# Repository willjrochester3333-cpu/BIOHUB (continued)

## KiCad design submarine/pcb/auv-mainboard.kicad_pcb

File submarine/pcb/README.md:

# PCB: the main board

A 150 x 60 mm, 2-layer carrier board for the ESP32-S3-DevKitC-1. It handles battery input, the 15 A fuse, the
magnet-operated soft-latch power switch, a 3 A 5 V regulator, the LoRa radio socket, all sensor connectors,
the 4-in-1 ESC interface, switched outputs, and camera power and button control.
How it works is explained in [`../docs/02-electronics.md`](../docs/02-electronics.md).

| Top | Bottom |
|---|---|
|  |  |

## Files

| File | What it is |
|---|---|
| `auv-mainboard.kicad_pro / .kicad_sch / .kicad_pcb` | The KiCad project (opens in KiCad 7 or newer) |
| `auv.kicad_sym`, `auv.pretty/` | Project library: ESP32-S3-DevKitC-1 socket and E220 socket symbols and footprints |
| `output/auv-mainboard-gerbers.zip` | **Upload this to JLCPCB / PCBWay.** Gerbers + drill files |
| `output/auv-mainboard-bom.csv` | Board parts list with suggested part numbers and rough prices |
| `output/auv-mainboard-pos.csv` | Pick-and-place file (if you want the board assembled) |
| `output/auv-mainboard-schematic.pdf / .png` | Schematic |
| `output/auv-mainboard-layout.pdf` | Top copper + silkscreen plot |
| `output/board_top.png`, `board_bottom.png` | Realistic images made from the Gerber layers |
| `design.py` | **Source of truth**: every part, pin, net, position and net class |
| `generate_board.py` | Turns `design.py` into everything above |
| `render_board_images.py` | Builds the board images from KiCad's layer plots |
| `placement.json` | Part positions and sizes for the Blender model |

## Status

* Schematic netlist (exported by KiCad) matches `design.py`: **0 mismatches**.
* Placement check: no courtyard overlaps. Only low SMD parts (≤ 3 mm) sit under the socketed DevKit and LoRa module.
* Routing: Freerouting 2.5, plus hand-placed wide copper for the battery -> fuse -> MOSFET -> ESC path
  (2.5–3 mm tracks, with the ground return on the bottom layer) and the regulator's switch node.
  Ground pours on both layers, and no copper under the ESP32 antenna.
* KiCad DRC: **0 errors, 0 unconnected pads**. The remaining warnings are silkscreen cosmetics and footprint-library
  links that need KiCad's global library table, which a normal KiCad install has.
* Fab limits used: 0.15 mm minimum track, 0.2 mm clearance, 0.35 mm minimum drill, 0.4 mm copper-to-edge.

## Regenerate

Needs KiCad 7+ (`pcbnew` Python module and `kicad-cli`), Java 25 and the Freerouting 2.5 jar. The board images need
Python with `cairosvg` and `Pillow`.

```bash
FREEROUTING_JAR=/path/to/freerouting-2.5.0-executable.jar python3 generate_board.py all
```

Steps, which can also be run one at a time: `libs sch verify_sch check route drc outputs`.

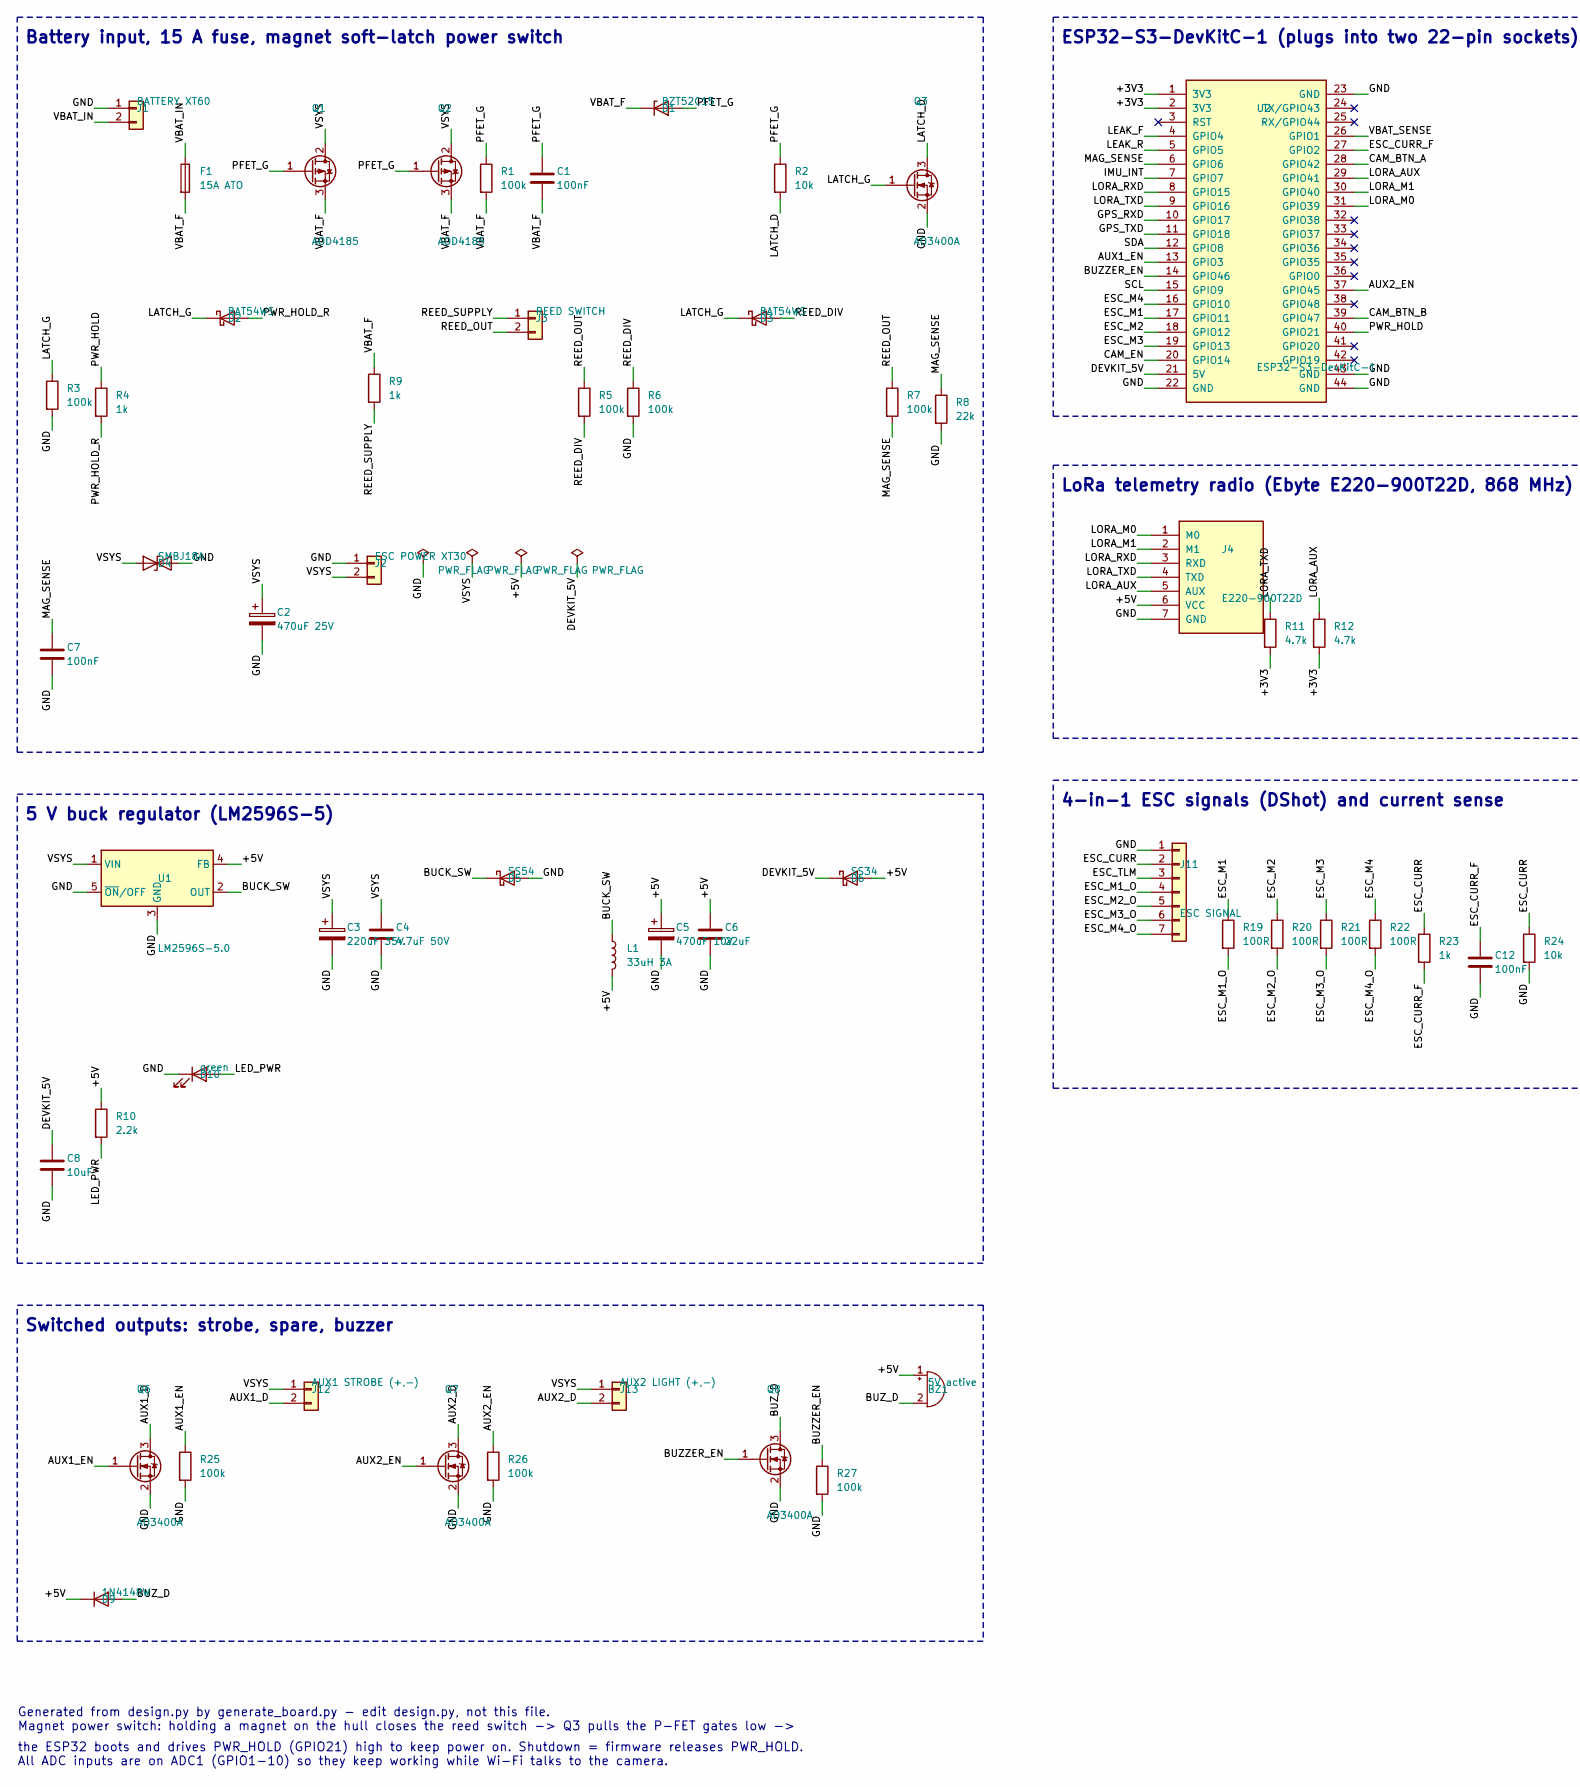
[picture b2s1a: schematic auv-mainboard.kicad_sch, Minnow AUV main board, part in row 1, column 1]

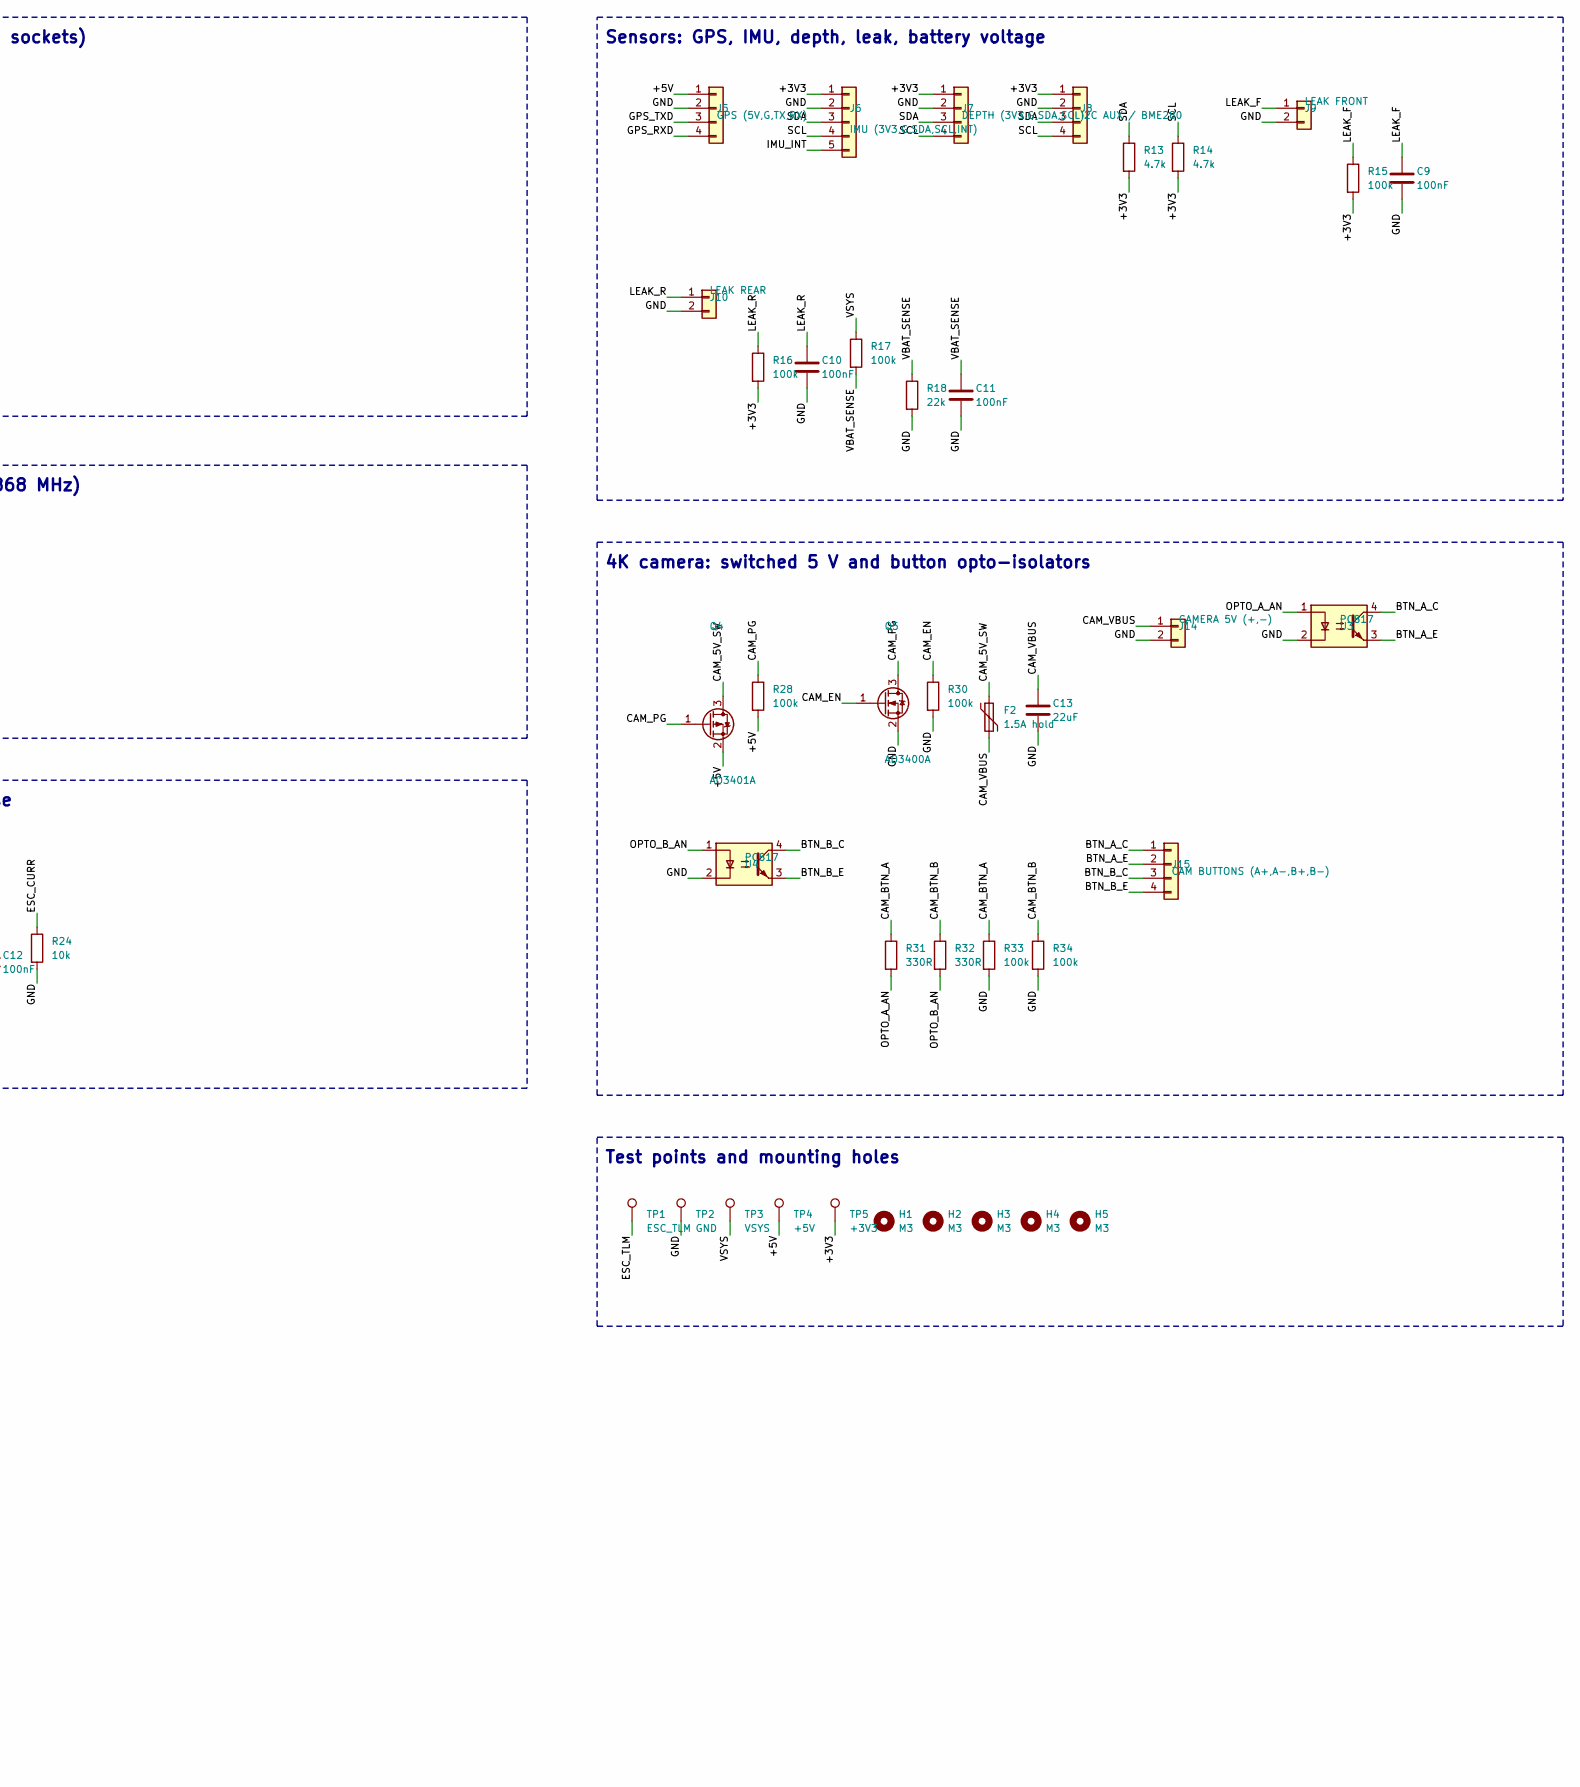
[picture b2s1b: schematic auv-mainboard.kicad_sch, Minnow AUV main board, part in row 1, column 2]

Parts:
BZ1: 5V active; Buzzer_12x9.5RM7.6; MPN 12 mm 5 V active buzzer (TMB12A05)
C1: 100nF; C_0805_2012Metric; MPN 0805 X7R 50V (soft start)
C2: 470uF 25V; CP_Radial_D10.0mm_P5.00mm; MPN 470 uF 25 V low-ESR electrolytic, 10 mm
C3: 220uF 35V; CP_Radial_D10.0mm_P5.00mm; MPN 220 uF 35 V low-ESR electrolytic, 10 mm
C4: 4.7uF 50V; C_1206_3216Metric; MPN 1206 X7R 50V
C5: 470uF 10V; CP_Radial_D8.0mm_P3.50mm; MPN 470 uF 10 V low-ESR electrolytic, 8 mm
C6, C13: 22uF; C_1206_3216Metric; MPN 1206 X5R 16V
C7, C9, C10, C11, C12: 100nF; C_0805_2012Metric; MPN 0805 X7R 50V
C8: 10uF; C_1206_3216Metric; MPN 1206 X5R 16V
D1: BZT52C15; D_SOD-123; MPN BZT52C15 15 V Zener SOD-123 (gate clamp)
D2, D3: BAT54WS; D_SOD-323; MPN BAT54WS Schottky SOD-323
D4: SMBJ18A; D_SMB; MPN SMBJ18A unidirectional TVS (ESC spikes)
D5: SS54; D_SMC; MPN SS54 5 A 40 V Schottky, SMC
D6: SS34; D_SMA; MPN SS34 3 A Schottky, SMA (stops USB back-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
D9: 1N4148W; D_SOD-123; MPN 1N4148W SOD-123
D10: green; LED_0805_2012Metric; MPN 0805 green LED (5 V present)
F1: 15A ATO; Fuseholder_Blade_ATO_Littelfuse_Pudenz_2_Pin; MPN ATO/ATC PCB fuse clip pair + 15 A blade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
F2: 1.5A hold; Fuse_1812_4532Metric; MPN 1812 PTC resettable fuse, 1.5 A hold
H1, H2, H3, H4, H5: M3; MountingHole_3.2mm_M3; MPN M3 mounting hole
J1: BATTERY XT60; AMASS_XT60PW-M_1x02_P7.20mm_Horizontal; MPN AMASS XT60PW-M (male, PCB, right angle)
J2: ESC POWER XT30; AMASS_XT30PW-F_1x02_P2.50mm_Horizontal; MPN AMASS XT30PW-F (female, PCB, right angl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
J3: REED SWITCH; JST_PH_B2B-PH-K_1x02_P2.00mm_Vertical; MPN JST PH 2-pin + glass reed switch (norma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
J4: E220-900T22D; E220-900T22D_Socket; MPN Ebyte E220-900T22D (868 MHz LoRa, UART)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
J5: GPS (5V,G,TX,RX); JST_PH_B4B-PH-K_1x04_P2.00mm_Vertical; MPN JST PH 4-pin to the BN-220 GPS in the m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
J6: IMU (3V3,G,SDA,SCL,INT); JST_PH_B5B-PH-K_1x05_P2.00mm_Vertical; MPN JST PH 5-pin vertical B5B-PH-K
J7: DEPTH (3V3,G,SDA,SCL); JST_PH_B4B-PH-K_1x04_P2.00mm_Vertical; MPN JST PH 4-pin vertical B4B-PH-K
J8: I2C AUX / BME280; JST_PH_B4B-PH-K_1x04_P2.00mm_Vertical; MPN JST PH 4-pin vertical B4B-PH-K
J9: LEAK FRONT; JST_PH_B2B-PH-K_1x02_P2.00mm_Vertical; MPN JST PH 2-pin vertical B2B-PH-K
J10: LEAK REAR; JST_PH_B2B-PH-K_1x02_P2.00mm_Vertical; MPN JST PH 2-pin vertical B2B-PH-K
J11: ESC SIGNAL; JST_PH_B7B-PH-K_1x07_P2.00mm_Vertical; MPN JST PH 7-pin; re-pin the ESC harness to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
J12: AUX1 STROBE (+,-); JST_XH_B2B-XH-A_1x02_P2.50mm_Vertical; MPN JST XH 2-pin to the strobe LED in the m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
J13: AUX2 LIGHT (+,-); JST_XH_B2B-XH-A_1x02_P2.50mm_Vertical; MPN JST XH 2-pin spare switched output (lig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
J14: CAMERA 5V (+,-); JST_XH_B2B-XH-A_1x02_P2.50mm_Vertical; MPN JST XH 2-pin to a USB-A female breakout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
J15: CAM BUTTONS (A+,A-,B+,B-); JST_PH_B4B-PH-K_1x04_P2.00mm_Vertical; MPN JST PH 4-pin, wires soldered across the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
L1: 33uH 3A; L_Bourns_SRR1260; MPN Bourns SRR1260-330M (33 uH, >3 A)
Q1: AOD4185; TO-252-2; MPN AOD4185 P-MOSFET -40V -40A DPAK (or SQD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
Q2: AOD4185; TO-252-2; MPN second FET in parallel halves the heat 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
Q3, Q5, Q6, Q7, Q8: AO3400A; SOT-23; MPN AO3400A N-MOSFET 30V 5.7A SOT-23 (logic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
Q4: AO3401A; SOT-23; MPN AO3401A P-MOSFET -30V -4A SOT-23
R1, R3, R5, R6, R7, R15, R16, R25, R26, R27, R28, R30, R33, R34: 100k; R_0805_2012Metric; MPN 0805 1% thick film
R2: 10k; R_0805_2012Metric; MPN 0805 1% thick film
R4, R23: 1k; R_0805_2012Metric; MPN 0805 1% thick film
R8: 22k; R_0805_2012Metric; MPN 0805 1% thick film
R9: 1k; R_0805_2012Metric; MPN 0805 (limits current if the reed lead s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
R10: 2.2k; R_0805_2012Metric; MPN 0805 1% thick film
R11, R12, R13, R14: 4.7k; R_0805_2012Metric; MPN 0805 1% thick film
R17: 100k; R_0805_2012Metric; MPN 0805 1% (battery divider top)
R18: 22k; R_0805_2012Metric; MPN 0805 1% (battery divider bottom)
R19, R20, R21, R22: 100R; R_0805_2012Metric; MPN 0805 1% thick film
R24: 10k; R_0805_2012Metric; MPN 0805 (holds the input low if no ESC)
R31, R32: 330R; R_0805_2012Metric; MPN 0805 1% thick film
TP1: ESC_TLM; TestPoint_Pad_D2.0mm; MPN test pad
TP2: GND; TestPoint_Pad_D2.0mm; MPN test pad
TP3: VSYS; TestPoint_Pad_D2.0mm; MPN test pad
TP4: +5V; TestPoint_Pad_D2.0mm; MPN test pad
TP5: +3V3; TestPoint_Pad_D2.0mm; MPN test pad
U1: LM2596S-5.0; TO-263-5_TabPin3; MPN LM2596S-5.0 3 A buck, TO-263-5
U2: ESP32-S3-DevKitC-1; ESP32-S3-DevKitC-1_Socket; MPN Espressif ESP32-S3-DevKitC-1 (N8R8 or N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
U3, U4: PC817; DIP-4_W7.62mm; MPN PC817 opto-isolator DIP-4 (presses came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

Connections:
+3V3: J6.1, J7.1, J8.1, R11.2, R12.2, R13.2, R14.2, R15.2, R16.2, TP5.1, U2.1 (3V3), U2.2 (3V3)
+5V: BZ1.1 (+), C5.1, C6.1, D6.2 (A), D9.1 (K), J4.6 (VCC), J5.1, L1.2, Q4.2 (S), R10.1, R28.2, TP4.1, U1.4 (FB)
AUX1_D: J12.2, Q6.3 (D)
AUX1_EN: Q6.1 (G), R25.1, U2.13 (GPIO3)
AUX2_D: J13.2, Q7.3 (D)
AUX2_EN: Q7.1 (G), R26.1, U2.37 (GPIO45)
BTN_A_C: J15.1, U3.4
BTN_A_E: J15.2, U3.3
BTN_B_C: J15.3, U4.4
BTN_B_E: J15.4, U4.3
BUCK_SW: D5.1 (K), L1.1, U1.2 (OUT)
CAM_5V_SW: F2.1, Q4.3 (D)
CAM_BTN_A: R31.1, R33.1, U2.28 (GPIO42)
CAM_BTN_B: R32.1, R34.1, U2.39 (GPIO47)
CAM_EN: Q5.1 (G), R30.1, U2.20 (GPIO14)
CAM_PG: Q4.1 (G), Q5.3 (D), R28.1
CAM_VBUS: C13.1, F2.2, J14.1
DEVKIT_5V: C8.1, D6.1 (K), U2.21 (5V)
ESC_CURR: J11.2, R23.1, R24.1
ESC_CURR_F: C12.1, R23.2, U2.27 (GPIO2)
ESC_M1: R19.1, U2.17 (GPIO11)
ESC_M1_O: J11.4, R19.2
ESC_M2: R20.1, U2.18 (GPIO12)
ESC_M2_O: J11.5, R20.2
ESC_M3: R21.1, U2.19 (GPIO13)
ESC_M3_O: J11.6, R21.2
ESC_M4: R22.1, U2.16 (GPIO10)
ESC_M4_O: J11.7, R22.2
ESC_TLM: J11.3, TP1.1
GND: C2.2, C3.2, C4.2, C5.2, C6.2, C7.2, C8.2, C9.2, C10.2, C11.2, C12.2, C13.2, D4.2 (A2), D5.2 (A), D10.1 (K), J1.1, J2.1, J4.7 (GND), J5.2, J6.2, J7.2, J8.2, J9.2, J10.2, J11.1, J14.2, Q3.2 (S), Q5.2 (S), Q6.2 (S), Q7.2 (S), Q8.2 (S), R3.2, R6.2, R8.2, R18.2, R24.2, R25.2, R26.2, R27.2, R30.2, R33.2, R34.2, TP2.1, U1.3 (GND), U1.5 (~ON/OFF), U2.22 (GND), U2.23 (GND), U2.43 (GND), U2.44 (GND), U3.2, U4.2
GPS_RXD: J5.4, U2.10 (GPIO17)
GPS_TXD: J5.3, U2.11 (GPIO18)
IMU_INT: J6.5, U2.7 (GPIO7)
LATCH_D: Q3.3 (D), R2.2
LATCH_G: D2.1 (K), D3.1 (K), Q3.1 (G), R3.1
LEAK_F: C9.1, J9.1, R15.1, U2.4 (GPIO4)
LEAK_R: C10.1, J10.1, R16.1, U2.5 (GPIO5)
LED_PWR: D10.2 (A), R10.2
LORA_AUX: J4.5 (AUX), R12.1, U2.29 (GPIO41)
LORA_M0: J4.1 (M0), U2.31 (GPIO39)
LORA_M1: J4.2 (M1), U2.30 (GPIO40)
LORA_RXD: J4.3 (RXD), U2.8 (GPIO15)
LORA_TXD: J4.4 (TXD), R11.1, U2.9 (GPIO16)
MAG_SENSE: C7.1, R7.2, R8.1, U2.6 (GPIO6)
unnamed: BZ1.2 (-), D9.2 (A), Q8.3 (D)
unnamed: Q8.1 (G), R27.1, U2.14 (GPIO46)
OPTO_A_AN: R31.2, U3.1
OPTO_B_AN: R32.2, U4.1
PFET_G: C1.1, D1.2 (A), Q1.1 (G), Q2.1 (G), R1.1, R2.1
PWR_HOLD: R4.1, U2.40 (GPIO21)
PWR_HOLD_R: D2.2 (A), R4.2
REED_DIV: D3.2 (A), R5.2, R6.1
REED_OUT: J3.2, R5.1, R7.1
REED_SUPPLY: J3.1, R9.2
SCL: J6.4, J7.4, J8.4, R14.1, U2.15 (GPIO9)
SDA: J6.3, J7.3, J8.3, R13.1, U2.12 (GPIO8)
VBAT_F: C1.2, D1.1 (K), F1.2, Q1.3 (S), Q2.3 (S), R1.2, R9.1
VBAT_IN: F1.1, J1.2
VBAT_SENSE: C11.1, R17.2, R18.1, U2.26 (GPIO1)
VSYS: C2.1, C3.1, C4.1, D4.1 (A1), J2.2, J12.1, J13.1, Q1.2 (D), Q2.2 (D), R17.1, TP3.1, U1.1 (VIN)

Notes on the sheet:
Battery input, 15 A fuse, magnet soft-latch power switch
5 V buck regulator (LM2596S-5)
Switched outputs: strobe, spare, buzzer
ESP32-S3-DevKitC-1 (plugs into two 22-pin sockets)
LoRa telemetry radio (Ebyte E220-900T22D, 868 MHz)
4-in-1 ESC signals (DShot) and current sense
Sensors: GPS, IMU, depth, leak, battery voltage
4K camera: switched 5 V and button opto-isolators
Test points and mounting holes
Generated from design.py by generate_board.py - edit design.py, not this file.
Magnet power switch: holding a magnet on the hull closes the reed switch -> Q3 pulls the P-FET gates low ->
the ESP32 boots and drives PWR_HOLD (GPIO21) high to keep power on. Shutdown = firmware releases PWR_HOLD.
All ADC inputs are on ADC1 (GPIO1-10) so they keep working while Wi-Fi talks to the camera.

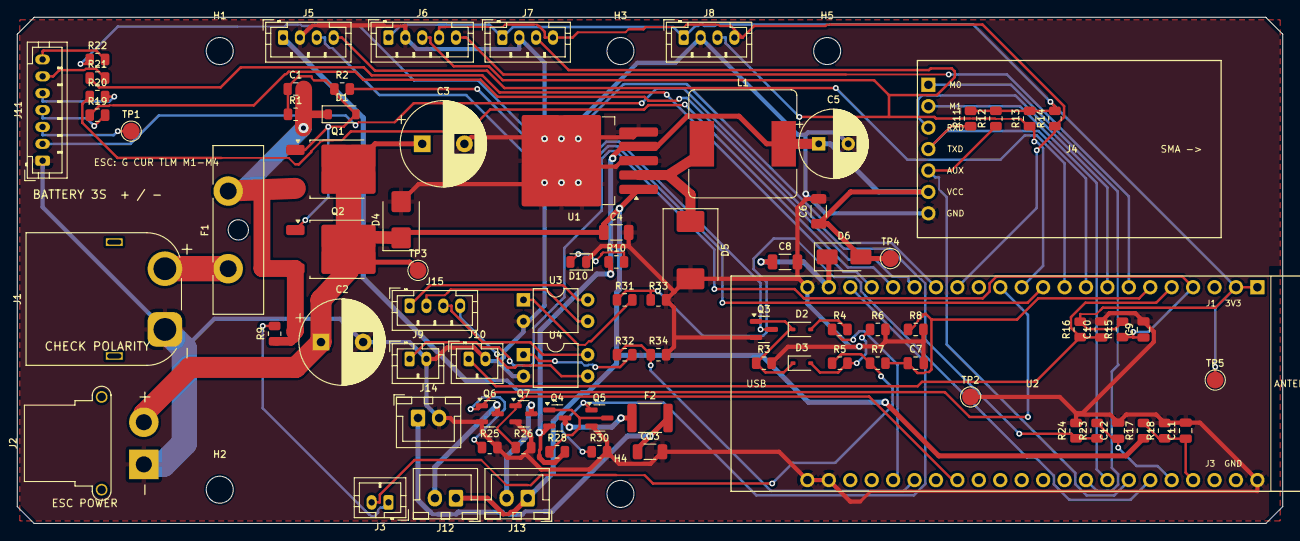
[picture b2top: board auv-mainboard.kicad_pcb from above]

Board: 2 copper layers, 150.0 x 60.0 mm, 91 parts (0 on the bottom side), 58 nets.

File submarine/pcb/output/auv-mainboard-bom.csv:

refs,qty,value,footprint,part,unit_gbp,line_gbp,note
C1,1,100nF,Capacitor_SMD:C_0805_2012Metric,0805 X7R 50V (soft start),0.03,0.03,
C7 C9 C10 C11 C12,5,100nF,Capacitor_SMD:C_0805_2012Metric,0805 X7R 50V,0.03,0.15,
C8,1,10uF,Capacitor_SMD:C_1206_3216Metric,1206 X5R 16V,0.10,0.10,
C6 C13,2,22uF,Capacitor_SMD:C_1206_3216Metric,1206 X5R 16V,0.10,0.20,
C4,1,4.7uF 50V,Capacitor_SMD:C_1206_3216Metric,1206 X7R 50V,0.10,0.10,
C3,1,220uF 35V,Capacitor_THT:CP_Radial_D10.0mm_P5.00mm,"220 uF 35 V low-ESR electrolytic, 10 mm",0.30,0.30,
C2,1,470uF 25V,Capacitor_THT:CP_Radial_D10.0mm_P5.00mm,"470 uF 25 V low-ESR electrolytic, 10 mm",0.30,0.30,
C5,1,470uF 10V,Capacitor_THT:CP_Radial_D8.0mm_P3.50mm,"470 uF 10 V low-ESR electrolytic, 8 mm",0.20,0.20,
J2,1,ESC POWER XT30,Connector_AMASS:AMASS_XT30PW-F_1x02_P2.50mm_Horizontal,"AMASS XT30PW-F (female, PCB, right angle)",0.60,0.60,
J1,1,BATTERY XT60,Connector_AMASS:AMASS_XT60PW-M_1x02_P7.20mm_Horizontal,"AMASS XT60PW-M (male, PCB, right angle)",0.90,0.90,
J9,1,LEAK FRONT,Connector_JST:JST_PH_B2B-PH-K_1x02_P2.00mm_Vertical,JST PH 2-pin vertical B2B-PH-K,0.15,0.15,
J10,1,LEAK REAR,Connector_JST:JST_PH_B2B-PH-K_1x02_P2.00mm_Vertical,JST PH 2-pin vertical B2B-PH-K,0.15,0.15,
J3,1,REED SWITCH,Connector_JST:JST_PH_B2B-PH-K_1x02_P2.00mm_Vertical,JST PH 2-pin + glass reed switch (normally open) on the hull wall,0.15,0.15,
J15,1,"CAM BUTTONS (A+,A-,B+,B-)",Connector_JST:JST_PH_B4B-PH-K_1x04_P2.00mm_Vertical,"JST PH 4-pin, wires soldered across the camera buttons (optional)",0.15,0.15,
J7,1,"DEPTH (3V3,G,SDA,SCL)",Connector_JST:JST_PH_B4B-PH-K_1x04_P2.00mm_Vertical,JST PH 4-pin vertical B4B-PH-K,0.15,0.15,
J5,1,"GPS (5V,G,TX,RX)",Connector_JST:JST_PH_B4B-PH-K_1x04_P2.00mm_Vertical,JST PH 4-pin to the BN-220 GPS in the mast,0.15,0.15,
J8,1,I2C AUX / BME280,Connector_JST:JST_PH_B4B-PH-K_1x04_P2.00mm_Vertical,JST PH 4-pin vertical B4B-PH-K,0.15,0.15,
J6,1,"IMU (3V3,G,SDA,SCL,INT)",Connector_JST:JST_PH_B5B-PH-K_1x05_P2.00mm_Vertical,JST PH 5-pin vertical B5B-PH-K,0.15,0.15,
J11,1,ESC SIGNAL,Connector_JST:JST_PH_B7B-PH-K_1x07_P2.00mm_Vertical,JST PH 7-pin; re-pin the ESC harness to match the silkscreen,0.15,0.15,
J12,1,"AUX1 STROBE (+,-)",Connector_JST:JST_XH_B2B-XH-A_1x02_P2.50mm_Vertical,JST XH 2-pin to the strobe LED in the mast,0.15,0.15,
J13,1,"AUX2 LIGHT (+,-)",Connector_JST:JST_XH_B2B-XH-A_1x02_P2.50mm_Vertical,"JST XH 2-pin spare switched output (lights, pump)",0.15,0.15,
J14,1,"CAMERA 5V (+,-)",Connector_JST:JST_XH_B2B-XH-A_1x02_P2.50mm_Vertical,JST XH 2-pin to a USB-A female breakout (bridge D+ to D-) for the camera cable,0.15,0.15,
D6,1,SS34,Diode_SMD:D_SMA,"SS34 3 A Schottky, SMA (stops USB back-feed)",0.08,0.08,
D4,1,SMBJ18A,Diode_SMD:D_SMB,SMBJ18A unidirectional TVS (ESC spikes),0.20,0.20,
D5,1,SS54,Diode_SMD:D_SMC,"SS54 5 A 40 V Schottky, SMC",0.30,0.30,
D1,1,BZT52C15,Diode_SMD:D_SOD-123,BZT52C15 15 V Zener SOD-123 (gate clamp),0.05,0.05,
D2 D3,2,BAT54WS,Diode_SMD:D_SOD-323,BAT54WS Schottky SOD-323,0.05,0.10,
F2,1,1.5A hold,Fuse:Fuse_1812_4532Metric,"1812 PTC resettable fuse, 1.5 A hold",0.20,0.20,
F1,1,15A ATO,Fuse:Fuseholder_Blade_ATO_Littelfuse_Pudenz_2_Pin,ATO/ATC PCB fuse clip pair + 15 A blade fuse,1.20,1.20,fuse clips + 15 A ATO blade fuse
L1,1,33uH 3A,Inductor_SMD:L_Bourns_SRR1260,"Bourns SRR1260-330M (33 uH, >3 A)",0.90,0.90,
D10,1,green,LED_SMD:LED_0805_2012Metric,0805 green LED (5 V present),0.05,0.05,
U3,1,PC817,Package_DIP:DIP-4_W7.62mm,PC817 opto-isolator DIP-4 (presses camera button A),0.15,0.15,
U4,1,PC817,Package_DIP:DIP-4_W7.62mm,PC817 opto-isolator DIP-4 (presses camera button B),0.15,0.15,
Q3 Q5 Q6 Q7,4,AO3400A,Package_TO_SOT_SMD:SOT-23,AO3400A N-MOSFET 30V 5.7A SOT-23 (logic level),0.10,0.40,
Q4,1,AO3401A,Package_TO_SOT_SMD:SOT-23,AO3401A P-MOSFET -30V -4A SOT-23,0.10,0.10,
Q1,1,AOD4185,Package_TO_SOT_SMD:TO-252-2,AOD4185 P-MOSFET -40V -40A DPAK (or SQD40031EL / IPD50P04P4L-11),0.60,0.60,
Q2,1,AOD4185,Package_TO_SOT_SMD:TO-252-2,second FET in parallel halves the heat (optional for <8 A),0.60,0.60,
U1,1,LM2596S-5.0,Package_TO_SOT_SMD:TO-263-5_TabPin3,"LM2596S-5.0 3 A buck, TO-263-5",1.20,1.20,
R19 R20 R21 R22,4,100R,Resistor_SMD:R_0805_2012Metric,0805 1% thick film,0.02,0.08,
R1 R3 R5 R6 R7 R15 R16 R25 R26 R28 R30 R33 R34,13,100k,Resistor_SMD:R_0805_2012Metric,0805 1% thick film,0.02,0.26,
R17,1,100k,Resistor_SMD:R_0805_2012Metric,0805 1% (battery divider top),0.02,0.02,
R2,1,10k,Resistor_SMD:R_0805_2012Metric,0805 1% thick film,0.02,0.02,
R24,1,10k,Resistor_SMD:R_0805_2012Metric,0805 (holds the input low if no ESC),0.02,0.02,
R4 R23,2,1k,Resistor_SMD:R_0805_2012Metric,0805 1% thick film,0.02,0.04,
R9,1,1k,Resistor_SMD:R_0805_2012Metric,0805 (limits current if the reed lead shorts),0.02,0.02,
R10,1,2.2k,Resistor_SMD:R_0805_2012Metric,0805 1% thick film,0.02,0.02,
R8,1,22k,Resistor_SMD:R_0805_2012Metric,0805 1% thick film,0.02,0.02,
R18,1,22k,Resistor_SMD:R_0805_2012Metric,0805 1% (battery divider bottom),0.02,0.02,
R31 R32,2,330R,Resistor_SMD:R_0805_2012Metric,0805 1% thick film,0.02,0.04,
R11 R12 R13 R14,4,4.7k,Resistor_SMD:R_0805_2012Metric,0805 1% thick film,0.02,0.08,
J4,1,E220-900T22D,auv:E220-900T22D_Socket,"Ebyte E220-900T22D (868 MHz LoRa, UART) on a 7-pin female header",0.25,0.25,module itself is in the main BOM; price = 7-pin female header
U2,1,ESP32-S3-DevKitC-1,auv:ESP32-S3-DevKitC-1_Socket,Espressif ESP32-S3-DevKitC-1 (N8R8 or N16R8) on 2 x 22-pin 2.54 mm female headers,0.80,0.80,module itself is in the main BOM; price = 2x 22-pin female headers

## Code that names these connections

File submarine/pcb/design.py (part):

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# J3 = G,TX,RX,1,2,42,41,40,39,38,37,36,35,0,45,48,47,21,20,19,G,G)
# Footprint pad n = J1 pin n, pad 22+n = J3 pin n.
# ---------------------------------------------------------------------------
DEVKIT_J1 = ['3V3', '3V3', 'RST', 'GPIO4', 'GPIO5', 'GPIO6', 'GPIO7', 'GPIO15', 'GPIO16', 'GPIO17',
             'GPIO18', 'GPIO8', 'GPIO3', 'GPIO46', 'GPIO9', 'GPIO10', 'GPIO11', 'GPIO12', 'GPIO13',
             'GPIO14', '5V', 'GND']
DEVKIT_J3 = ['GND', 'TX/GPIO43', 'RX/GPIO44', 'GPIO1', 'GPIO2', 'GPIO42', 'GPIO41', 'GPIO40', 'GPIO39',
             'GPIO38', 'GPIO37', 'GPIO36', 'GPIO35', 'GPIO0', 'GPIO45', 'GPIO48', 'GPIO47', 'GPIO21',
             'GPIO20', 'GPIO19', 'GND', 'GND']

GPIO_NET = {
    # ADC1 (usable with Wi-Fi on)
    'GPIO1': 'VBAT_SENSE', 'GPIO2': 'ESC_CURR_F', 'GPIO4': 'LEAK_F', 'GPIO5': 'LEAK_R', 'GPIO6': 'MAG_SENSE',
    # sensors and radios
    'GPIO7': 'IMU_INT', 'GPIO8': 'SDA', 'GPIO9': 'SCL',
    'GPIO15': 'LORA_RXD', 'GPIO16': 'LORA_TXD', 'GPIO17': 'GPS_RXD', 'GPIO18': 'GPS_TXD',
    'GPIO39': 'LORA_M0', 'GPIO40': 'LORA_M1', 'GPIO41': 'LORA_AUX',
    # thrusters (DShot via the RMT peripheral)
    'GPIO11': 'ESC_M1', 'GPIO12': 'ESC_M2', 'GPIO13': 'ESC_M3', 'GPIO10': 'ESC_M4',
    # camera, outputs, power latch
    'GPIO14': 'CAM_EN', 'GPIO42': 'CAM_BTN_A', 'GPIO47': 'CAM_BTN_B',
    'GPIO3': 'AUX1_EN', 'GPIO45': 'AUX2_EN', 'GPIO21': 'PWR_HOLD',   # GPIO46 left free (spare)
}


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PARTS = [
    # ---------------- power entry, fuse, soft-latch high-side switch --------------
    dict(ref='J1', sym='Connector_Generic:Conn_01x02', val='BATTERY XT60', fp='Connector_AMASS:AMASS_XT60PW-M_1x02_P7.20mm_Horizontal',
         pins={'1': 'GND', '2': 'VBAT_IN'}, pcb=(17.5, 37.0, 90), blk='power', mpn='AMASS XT60PW-M (male, PCB, right angle)'),
    dict(ref='F1', sym='Device:Fuse', val='15A ATO', fp='Fuse:Fuseholder_Blade_ATO_Littelfuse_Pudenz_2_Pin',
         pins={'1': 'VBAT_IN', '2': 'VBAT_F'}, pcb=(25.0, 29.8, 90), blk='power', mpn='ATO/ATC PCB fuse clip pair + 15 A blade fuse'),
    dict(ref='Q1', sym='Device:Q_PMOS_GDS', val='AOD4185', fp='Package_TO_SOT_SMD:TO-252-2',
         pins={'1': 'PFET_G', '2': 'VSYS', '3': 'VBAT_F'}, pcb=(38.0, 18.0, 0), blk='power',
         mpn='AOD4185 P-MOSFET -40V -40A DPAK (or SQD40031EL / IPD50P04P4L-11)'),
    dict(ref='Q2', sym='Device:Q_PMOS_GDS', val='AOD4185', fp='Package_TO_SOT_SMD:TO-252-2',
         pins={'1': 'PFET_G', '2': 'VSYS', '3': 'VBAT_F'}, pcb=(38.0, 27.5, 0), blk='power',
         mpn='second FET in parallel halves the heat (optional for <8 A)'),
    R('R1', '100k', 'PFET_G', 'VBAT_F', (33.0, 11.5, 0), 'power'),
    C('C1', '100nF', 'PFET_G', 'VBAT_F', (33.0, 8.5, 0), 'power', mpn='0805 X7R 50V (soft start)'),
    dict(ref='D1', sym='Device:D_Zener', val='BZT52C15', fp='Diode_SMD:D_SOD-123', pins={'1': 'VBAT_F', '2': 'PFET_G'},
         pcb=(38.5, 11.5, 0), blk='power', mpn='BZT52C15 15 V Zener SOD-123 (gate clamp)'),
    R('R2', '10k', 'PFET_G', 'LATCH_D', (38.5, 8.5, 0), 'power'),
    NFET('Q3', 'LATCH_G', 'GND', 'LATCH_D', (88.5, 37.0, 0), 'power'),
    R('R3', '100k', 'LATCH_G', 'GND', (88.5, 41.0, 0), 'power'),
    R('R4', '1k', 'PWR_HOLD', 'PWR_HOLD_R', (97.5, 37.0, 0), 'power'),
    dict(ref='D2', sym='Device:D_Schottky', val='BAT54WS', fp='Diode_SMD:D_SOD-323', pins={'1': 'LATCH_G', '2': 'PWR_HOLD_R'},
         pcb=(93.0, 37.0, 0), blk='power', mpn='BAT54WS Schottky SOD-323'),
    R('R9', '1k', 'VBAT_F', 'REED_SUPPLY', (30.5, 37.5, 90), 'power', mpn='0805 (limits current if the reed lead shorts)'),
    conn('J3', 2, ['REED_SUPPLY', 'REED_OUT'], (44.0, 57.5, 180), 'power', 'REED SWITCH',
         mpn='JST PH 2-pin + glass reed switch (normally open) on the hull wall'),
    R('R5', '100k', 'REED_OUT', 'REED_DIV', (97.5, 41.0, 0), 'power'),
    R('R6', '100k', 'REED_DIV', 'GND', (102.0, 37.0, 0), 'power'),
    dict(ref='D3', sym='Device:D_Schottky', val='BAT54WS', fp='Diode_SMD:D_SOD-323', pins={'1': 'LATCH_G', '2': 'REED_DIV'},
         pcb=(93.0, 41.0, 0), blk='power', mpn='BAT54WS Schottky SOD-323'),
    R('R7', '100k', 'REED_OUT', 'MAG_SENSE', (102.0, 41.0, 0), 'power'),
    R('R8', '22k', 'MAG_SENSE', 'GND', (106.5, 37.0, 0), 'power'),
    C('C7', '100nF', 'MAG_SENSE', 'GND', (106.5, 41.0, 0), 'power'),
    dict(ref='D4', sym='Device:D_TVS', val='SMBJ18A', fp='Diode_SMD:D_SMB', pins={'1': 'VSYS', '2': 'GND'},
         pcb=(45.5, 24.0, 90), blk='power', mpn='SMBJ18A unidirectional TVS (ESC spikes)'),
    dict(ref='C2', sym='Device:C_Polarized', val='470uF 25V', fp='Capacitor_THT:CP_Radial_D10.0mm_P5.00mm',
         pins={'1': 'VSYS', '2': 'GND'}, pcb=(36.0, 38.5, 0), blk='power', mpn='470 uF 25 V low-ESR electrolytic, 10 mm'),
    dict(ref='J2', sym='Connector_Generic:Conn_01x02', val='ESC POWER XT30', fp='Connector_AMASS:AMASS_XT30PW-F_1x02_P2.50mm_Horizontal',
         pins={'1': 'GND', '2': 'VSYS'}, pcb=(15.0, 53.0, 90), blk='power', mpn='AMASS XT30PW-F (female, PCB, right angle)'),
    # ---------------- 5 V buck regulator ---------------------------------------------
    dict(ref='U1', sym='Regulator_Switching:LM2596S-5', val='LM2596S-5.0', fp='Package_TO_SOT_SMD:TO-263-5_TabPin3',
         pins={'1': 'VSYS', '2': 'BUCK_SW', '3': 'GND', '4': '+5V', '5': 'GND'}, pcb=(66.0, 17.0, 180), blk='buck',
         mpn='LM2596S-5.0 3 A buck, TO-263-5'),
    dict(ref='C3', sym='Device:C_Polarized', val='220uF 35V', fp='Capacitor_THT:CP_Radial_D10.0mm_P5.00mm',
         pins={'1': 'VSYS', '2': 'GND'}, pcb=(48.0, 15.0, 0), blk='buck', mpn='220 uF 35 V low-ESR electrolytic, 10 mm'),
    C('C4', '4.7uF 50V', 'VSYS', 'GND', (71.0, 25.5, 0), 'buck', fp=C1206, mpn='1206 X7R 50V'),
    dict(ref='D5', sym='Device:D_Schottky', val='SS54', fp='Diode_SMD:D_SMC', pins={'1': 'BUCK_SW', '2': 'GND'},
         pcb=(79.8, 27.6, 270), blk='buck', mpn='SS54 5 A 40 V Schottky, SMC'),
    dict(ref='L1', sym='Device:L', val='33uH 3A', fp='Inductor_SMD:L_Bourns_SRR1260',
         pins={'1': 'BUCK_SW', '2': '+5V'}, pcb=(86.0, 15.0, 0), blk='buck', mpn='Bourns SRR1260-330M (33 uH, >3 A)'),
    dict(ref='C5', sym='Device:C_Polarized', val='470uF 10V', fp='Capacitor_THT:CP_Radial_D8.0mm_P3.50mm',
         pins={'1': '+5V', '2': 'GND'}, pcb=(95.0, 15.0, 0), blk='buck', mpn='470 uF 10 V low-ESR electrolytic, 8 mm'),
    C('C6', '22uF', '+5V', 'GND', (95.0, 23.0, 90), 'buck', fp=C1206, mpn='1206 X5R 16V'),
    dict(ref='D6', sym='Device:D_Schottky', val='SS34', fp='Diode_SMD:D_SMA', pins={'1': 'DEVKIT_5V', '2': '+5V'},
         pcb=(98.0, 28.4, 0), blk='buck', mpn='SS34 3 A Schottky, SMA (stops USB back-feed)'),
    C('C8', '10uF', 'DEVKIT_5V', 'GND', (91.0, 29.0, 0), 'buck', fp=C1206, mpn='1206 X5R 16V'),
    R('R10', '2.2k', '+5V', 'LED_PWR', (71.0, 29.0, 0), 'buck'),
    dict(ref='D10', sym='Device:LED', val='green', fp='LED_SMD:LED_0805_2012Metric', pins={'1': 'GND', '2': 'LED_PWR'},
         pcb=(66.5, 29.0, 180), blk='buck', mpn='0805 green LED (5 V present)'),
    # ---------------- MCU ---------------------------------------------------------------
    dict(ref='U2', sym='auv:ESP32-S3-DevKitC-1', val='ESP32-S3-DevKitC-1', fp='auv:ESP32-S3-DevKitC-1_Socket',
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         mpn='Espressif ESP32-S3-DevKitC-1 (N8R8 or N16R8) on 2 x 22-pin 2.54 mm female headers'),
    # ---------------- LoRa radio ---------------------------------------------------------
    dict(ref='J4', sym='auv:E220-900T22D', val='E220-900T22D', fp='auv:E220-900T22D_Socket',
         pins={'1': 'LORA_M0', '2': 'LORA_M1', '3': 'LORA_RXD', '4': 'LORA_TXD', '5': 'LORA_AUX', '6': '+5V', '7': 'GND'},
         pcb=(108.0, 8.0, 0), blk='lora', mpn='Ebyte E220-900T22D (868 MHz LoRa, UART) on a 7-pin female header'),
    R('R11', '4.7k', 'LORA_TXD', '+3V3', (113.0, 12.0, 90), 'lora'),
    R('R12', '4.7k', 'LORA_AUX', '+3V3', (116.0, 12.0, 90), 'lora'),
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    conn('J13', 2, ['VSYS', 'AUX2_D'], (60.5, 57.0, 180), 'outputs', 'AUX2 LIGHT (+,-)', xh=True,
         mpn='JST XH 2-pin spare switched output (lights, pump)'),
    # ---------------- camera power switch and button opto-isolators ----------------------
    dict(ref='Q4', sym='Device:Q_PMOS_GSD', val='AO3401A', fp=SOT23, pins={'1': 'CAM_PG', '2': '+5V', '3': 'CAM_5V_SW'},
         pcb=(64.0, 47.5, 0), blk='camera', mpn='AO3401A P-MOSFET -30V -4A SOT-23'),
    R('R28', '100k', 'CAM_PG', '+5V', (64.0, 51.5, 0), 'camera'),
    NFET('Q5', 'CAM_EN', 'GND', 'CAM_PG', (69.0, 47.5, 0), 'camera'),
    R('R30', '100k', 'CAM_EN', 'GND', (69.0, 51.5, 0), 'camera'),
    dict(ref='F2', sym='Device:Polyfuse', val='1.5A hold', fp='Fuse:Fuse_1812_4532Metric', pins={'1': 'CAM_5V_SW', '2': 'CAM_VBUS'},
         pcb=(75.0, 47.5, 0), blk='camera', mpn='1812 PTC resettable fuse, 1.5 A hold'),
    C('C13', '22uF', 'CAM_VBUS', 'GND', (75.0, 51.5, 0), 'camera', fp=C1206, mpn='1206 X5R 16V'),
    conn('J14', 2, ['CAM_VBUS', 'GND'], (47.5, 47.5, 0), 'camera', 'CAMERA 5V (+,-)', xh=True,
         mpn='JST XH 2-pin to a USB-A female breakout (bridge D+ to D-) for the camera cable'),
    dict(ref='U3', sym='Isolator:PC817', val='PC817', fp='Package_DIP:DIP-4_W7.62mm',
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
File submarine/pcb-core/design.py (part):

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PARTS = [
    # ================= battery in, 15 A fuse, magnet soft-latch high-side switch =================
    dict(ref='J1', sym='Connector_Generic:Conn_01x02', val='BATTERY XT60', fp='Connector_AMASS:AMASS_XT60PW-M_1x02_P7.20mm_Horizontal',
         pins={'1': 'GND', '2': 'VBAT_IN'}, pcb=(17.5, 37.0, 90), blk='power', lcsc='C98732',
         mpn='AMASS XT60PW-M (male, PCB, right angle) - through-hole'),
    dict(ref='F1', sym='Device:Fuse', val='15A', fp='Fuse:Fuse_1206_3216Metric', pins={'1': 'VBAT_IN', '2': 'VBAT_F'},
         pcb=(22.6, 29.8, 0), blk='power', lcsc='C136356', mpn='JFC1206-2150FS 15 A 32 V fast fuse, 1206'),
    dict(ref='Q1', sym='Device:Q_PMOS_GDS', val='AOD4185', fp='Package_TO_SOT_SMD:TO-252-2',
         pins={'1': 'PFET_G', '2': 'VSYS', '3': 'VBAT_F'}, pcb=(38.0, 18.0, 0), blk='power', lcsc='C400894',
         mpn='AOD4185 P-MOSFET -40 V -40 A DPAK'),
    dict(ref='Q2', sym='Device:Q_PMOS_GDS', val='AOD4185', fp='Package_TO_SOT_SMD:TO-252-2',
         pins={'1': 'PFET_G', '2': 'VSYS', '3': 'VBAT_F'}, pcb=(38.0, 27.5, 0), blk='power', lcsc='C400894',
         mpn='AOD4185 P-MOSFET -40 V -40 A DPAK (in parallel with Q1: half the heat)'),
    R('R1', '100k', 'PFET_G', 'VBAT_F', (35.6, 12.35, 90), 'power', 'gate pull-up: FETs off'),
    C('C1', '100nF', 'PFET_G', 'VBAT_F', (33.4, 12.35, 90), 'power', note='soft start'),
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    R('R5', '100R', 'VBAT_F', 'VAON_IN', (18.0, 6.5, 90), 'power', 'spike filter'),
    C('C2', '1uF', 'VAON_IN', 'GND', (18.0, 2.9, 90), 'power'),
    dict(ref='U1', sym='Regulator_Linear:HT75xx-1-SOT89', val='HT7533-1', fp='Package_TO_SOT_SMD:SOT-89-3',
         pins={'1': 'GND', '2': 'VAON_IN', '3': 'VAON'}, pcb=(13.5, 4.0, 0), blk='power', lcsc='C14289',
         mpn='HT7533-1 3.3 V LDO, 30 V in, 2.5 uA, SOT-89'),
    C('C3', '1uF', 'VAON', 'GND', (13.5, 8.0, 0), 'power'),
    dict(ref='U2', sym='Sensor_Magnetic:SM351LT', val='SM351LT', fp=SOT23, pins={'1': 'VAON', '2': 'HALL_OUT', '3': 'GND'},
         pcb=(8.5, 2.3, 0), blk='power', lcsc='C80830',
         mpn='Honeywell SM351LT magnetoresistive switch, output low near a magnet, 0.36 uA'),
    C('C4', '100nF', 'VAON', 'GND', (8.5, 5.6, 0), 'power'),
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    SCHOTTKY_SMALL('D2', 'LATCH_G', 'HALL_ON', (8.7, 8.6, 0), 'power'),
    R('R7', '220k', 'HALL_OUT', 'MAG_SENSE', (8.7, 11.2, 0), 'power', 'magnet state to the ESP32'),
    # protection and bulk capacitance on the switched battery rail
    dict(ref='D3', sym='Device:D_TVS', val='SMBJ18A', fp='Diode_SMD:D_SMB', pins={'1': 'VSYS', '2': 'GND'},
         pcb=(46.5, 22.5, 90), blk='power', lcsc='C19077573', mpn='SMBJ18A unidirectional TVS (ESC spikes)'),
    dict(ref='C5', sym='Device:C_Polarized', val='100uF 35V', fp='Capacitor_SMD:CP_Elec_6.3x7.7',
         pins={'1': 'VSYS', '2': 'GND'}, pcb=(46.5, 31.0, 270), blk='power', lcsc='C72478',
         mpn='100 uF 35 V aluminium electrolytic, SMD 6.3 x 7.7 mm'),
    dict(ref='C6', sym='Device:C_Polarized', val='100uF 35V', fp='Capacitor_SMD:CP_Elec_6.3x7.7',
         pins={'1': 'VSYS', '2': 'GND'}, pcb=(46.5, 40.6, 270), blk='power', lcsc='C72478',
         mpn='100 uF 35 V aluminium electrolytic, SMD 6.3 x 7.7 mm'),
    dict(ref='J2', sym='Connector_Generic:Conn_01x02', val='ESC POWER XT30', fp='Connector_AMASS:AMASS_XT30UPB-F_1x02_P5.0mm_Vertical',
         pins={'1': 'GND', '2': 'VSYS'}, pcb=(8.0, 55.0, 90), blk='power', lcsc='C108769',
         mpn='AMASS XT30UPB-F (female, PCB, vertical) - through-hole'),
    R('R8', '100k', 'VSYS', 'VBAT_SENSE', (36.0, 35.0, 0), 'power', 'battery divider top'),
    R('R9', '22k', 'VBAT_SENSE', 'GND', (36.0, 37.4, 0), 'power', 'battery divider bottom'),
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
    # ================= 5 V / 3 A buck (TPS54302) =================
    dict(ref='U3', sym='Regulator_Switching:TPS54302', val='TPS54302', fp='Package_TO_SOT_SMD:SOT-23-6',
         pins={'1': 'GND', '2': 'BUCK_SW', '3': 'VSYS', '4': 'BUCK_FB', '5': 'BUCK_EN', '6': 'BUCK_BOOT'},
         pcb=(59.0, 31.0, 90), blk='buck', lcsc='C311983', mpn='TI TPS54302DDCR 3 A 28 V synchronous buck, SOT-23-6'),
    C('C8', '10uF', 'VSYS', 'GND', (63.3, 30.0, 0), 'buck', fp=C1206, note='50 V'),
    C('C9', '10uF', 'VSYS', 'GND', (63.3, 27.4, 0), 'buck', fp=C1206, note='50 V'),
    C('C10', '100nF', 'VSYS', 'GND', (63.3, 32.8, 0), 'buck'),
    C('C11', '100nF', 'BUCK_BOOT', 'BUCK_SW', (55.6, 31.0, 90), 'buck', note='bootstrap'),
    dict(ref='L1', sym='Device:L', val='12uH', fp='Inductor_SMD:L_Bourns_SRR1260', pins={'1': 'BUCK_SW', '2': '+5V'},
         pcb=(59.0, 41.5, 270), blk='buck', lcsc='C1329355', mpn='Bourns SRR1260-120M 12 uH 5 A shielded'),
    C('C12', '22uF', '+5V', 'GND', (67.6, 44.0, 90), 'buck', fp=C1206),
    C('C13', '22uF', '+5V', 'GND', (70.2, 44.0, 90), 'buck', fp=C1206),
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    R('R12', '100k', 'VSYS', 'BUCK_EN', (55.0, 26.0, 0), 'buck', 'starts at 6.6 V'),
    R('R13', '22k', 'BUCK_EN', 'GND', (55.0, 23.8, 0), 'buck'),
    R('R14', '2.2k', '+5V', 'LED_5V', (66.8, 51.9, 0), 'buck'),
    dict(ref='D4', sym='Device:LED', val='green', fp='LED_SMD:LED_0805_2012Metric', pins={'1': 'GND', '2': 'LED_5V'},
         pcb=(68.0, 49.5, 180), blk='buck', lcsc='C2297', mpn='green LED 0805 (5 V on)'),

    # ================= USB-C, USB serial, auto-program, 3.3 V =================
    dict(ref='J3', sym='Connector:USB_C_Receptacle_USB2.0_16P', val='USB-C', fp='Connector_USB:USB_C_Receptacle_HRO_TYPE-C-31-M-12',
         pins={'A1': 'GND', 'A12': 'GND', 'B1': 'GND', 'B12': 'GND', 'S1': 'GND', 'A4': 'USB_VBUS', 'A9': 'USB_VBUS',
               'B4': 'USB_VBUS', 'B9': 'USB_VBUS', 'A5': 'USB_CC1', 'B5': 'USB_CC2', 'A6': 'USB_DP', 'B6': 'USB_DP',
               'A7': 'USB_DN', 'B7': 'USB_DN', 'A8': None, 'B8': None},
         pcb=(112.0, 57.0, 0), blk='usb', lcsc='C165948', mpn='Korean Hroparts TYPE-C-31-M-12 USB-C receptacle'),
    R('R15', '5.1k', 'USB_CC1', 'GND', (110.0, 49.6, 90), 'usb', 'USB-C sink'),
    R('R16', '5.1k', 'USB_CC2', 'GND', (114.0, 49.6, 90), 'usb', 'USB-C sink'),
    dict(ref='U4', sym='Power_Protection:SRV05-4', val='SRV05-4', fp='Package_TO_SOT_SMD:SOT-23-6',
         pins={'1': 'USB_DP', '2': 'GND', '3': 'USB_DN', '4': None, '5': 'USB_VBUS', '6': None},
         pcb=(112.0, 45.5, 0), blk='usb', lcsc='C85364', mpn='SRV05-4 USB ESD protection, SOT-23-6'),
    C('C14', '10uF', 'USB_VBUS', 'GND', (119.5, 53.0, 90), 'usb'),
    dict(ref='D5', sym='Device:D_Schottky', val='SS34', fp='Diode_SMD:D_SMA', pins={'1': 'LDO_IN', '2': 'USB_VBUS'},
         pcb=(118.5, 45.5, 90), blk='usb', lcsc='C8678',
         mpn='SS34 3 A Schottky, SMA (USB powers only the 3.3 V side: never the battery side)'),
    dict(ref='D8', sym='Device:D_Schottky', val='SS34', fp='Diode_SMD:D_SMA', pins={'1': 'LDO_IN', '2': '+5V'},
         pcb=(112.0, 19.5, 90), blk='usb', lcsc='C8678', mpn='SS34 3 A Schottky, SMA (5 V -> 3.3 V regulator)'),
    dict(ref='U5', sym='Interface_USB:CH340C', val='CH340C', fp='Package_SO:SOIC-16_3.9x9.9mm_P1.27mm',
         pins={'1': 'GND', '2': 'ESP_RXD', '3': 'ESP_TXD', '4': '+3V3', '5': 'USB_DP', '6': 'USB_DN', '7': None,
               '8': None, '9': None, '10': None, '11': None, '12': None, '13': 'CH_DTR', '14': 'CH_RTS',
               '15': None, '16': '+3V3'},
         pcb=(104.0, 46.0, 0), blk='usb', lcsc='C84681', mpn='WCH CH340C USB-serial (no crystal), SOIC-16'),
    C('C15', '100nF', '+3V3', 'GND', (98.8, 46.0, 90), 'usb'),
    dict(ref='Q5', sym='Transistor_BJT:MMBT3904', val='MMBT3904', fp=SOT23, pins={'1': 'AP_B1', '2': 'CH_RTS', '3': 'ESP_EN'},
         pcb=(110.0, 38.5, 0), blk='usb', lcsc='C20526', mpn='MMBT3904 NPN SOT-23 (auto-reset)'),
    dict(ref='Q6', sym='Transistor_BJT:MMBT3904', val='MMBT3904', fp=SOT23, pins={'1': 'AP_B2', '2': 'CH_DTR', '3': 'ESP_IO0'},
         pcb=(114.5, 38.5, 0), blk='usb', lcsc='C20526', mpn='MMBT3904 NPN SOT-23 (auto-boot)'),
    R('R17', '10k', 'CH_DTR', 'AP_B1', (110.0, 42.0, 0), 'usb'),
    R('R18', '10k', 'CH_RTS', 'AP_B2', (114.5, 42.0, 0), 'usb'),
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    C('C16', '1uF', 'ESP_EN', 'GND', (135.0, 2.6, 0), 'usb', note='reset delay'),
    R('R20', '10k', '+3V3', 'ESP_IO0', (122.0, 31.5, 0), 'usb'),
    dict(ref='SW1', sym='Switch:SW_Push', val='RESET', fp='Button_Switch_SMD:SW_Push_1P1T_XKB_TS-1187A',
         pins={'1': 'ESP_EN', '2': 'GND'}, pcb=(114.0, 4.0, 0), blk='usb', lcsc='C318884', mpn='XKB TS-1187A-B-A-B tact switch'),
    dict(ref='SW2', sym='Switch:SW_Push', val='BOOT', fp='Button_Switch_SMD:SW_Push_1P1T_XKB_TS-1187A',
         pins={'1': 'ESP_IO0', '2': 'GND'}, pcb=(105.0, 4.0, 0), blk='usb', lcsc='C318884', mpn='XKB TS-1187A-B-A-B tact switch'),
    dict(ref='U6', sym='Regulator_Linear:AMS1117-3.3', val='AMS1117-3.3', fp='Package_TO_SOT_SMD:SOT-223-3_TabPin2',
         pins={'1': 'GND', '2': '+3V3', '3': 'LDO_IN'}, pcb=(119.0, 13.0, 0), blk='usb', lcsc='C6186',
         mpn='AMS1117-3.3 1 A LDO, SOT-223'),
    C('C17', '22uF', 'LDO_IN', 'GND', (112.0, 13.0, 90), 'usb', fp=C1206),
    C('C18', '22uF', '+3V3', 'GND', (119.0, 19.0, 0), 'usb', fp=C1206),
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    C('C19', '10uF', '+3V3', 'GND', (131.0, 2.6, 0), 'mcu'),
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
